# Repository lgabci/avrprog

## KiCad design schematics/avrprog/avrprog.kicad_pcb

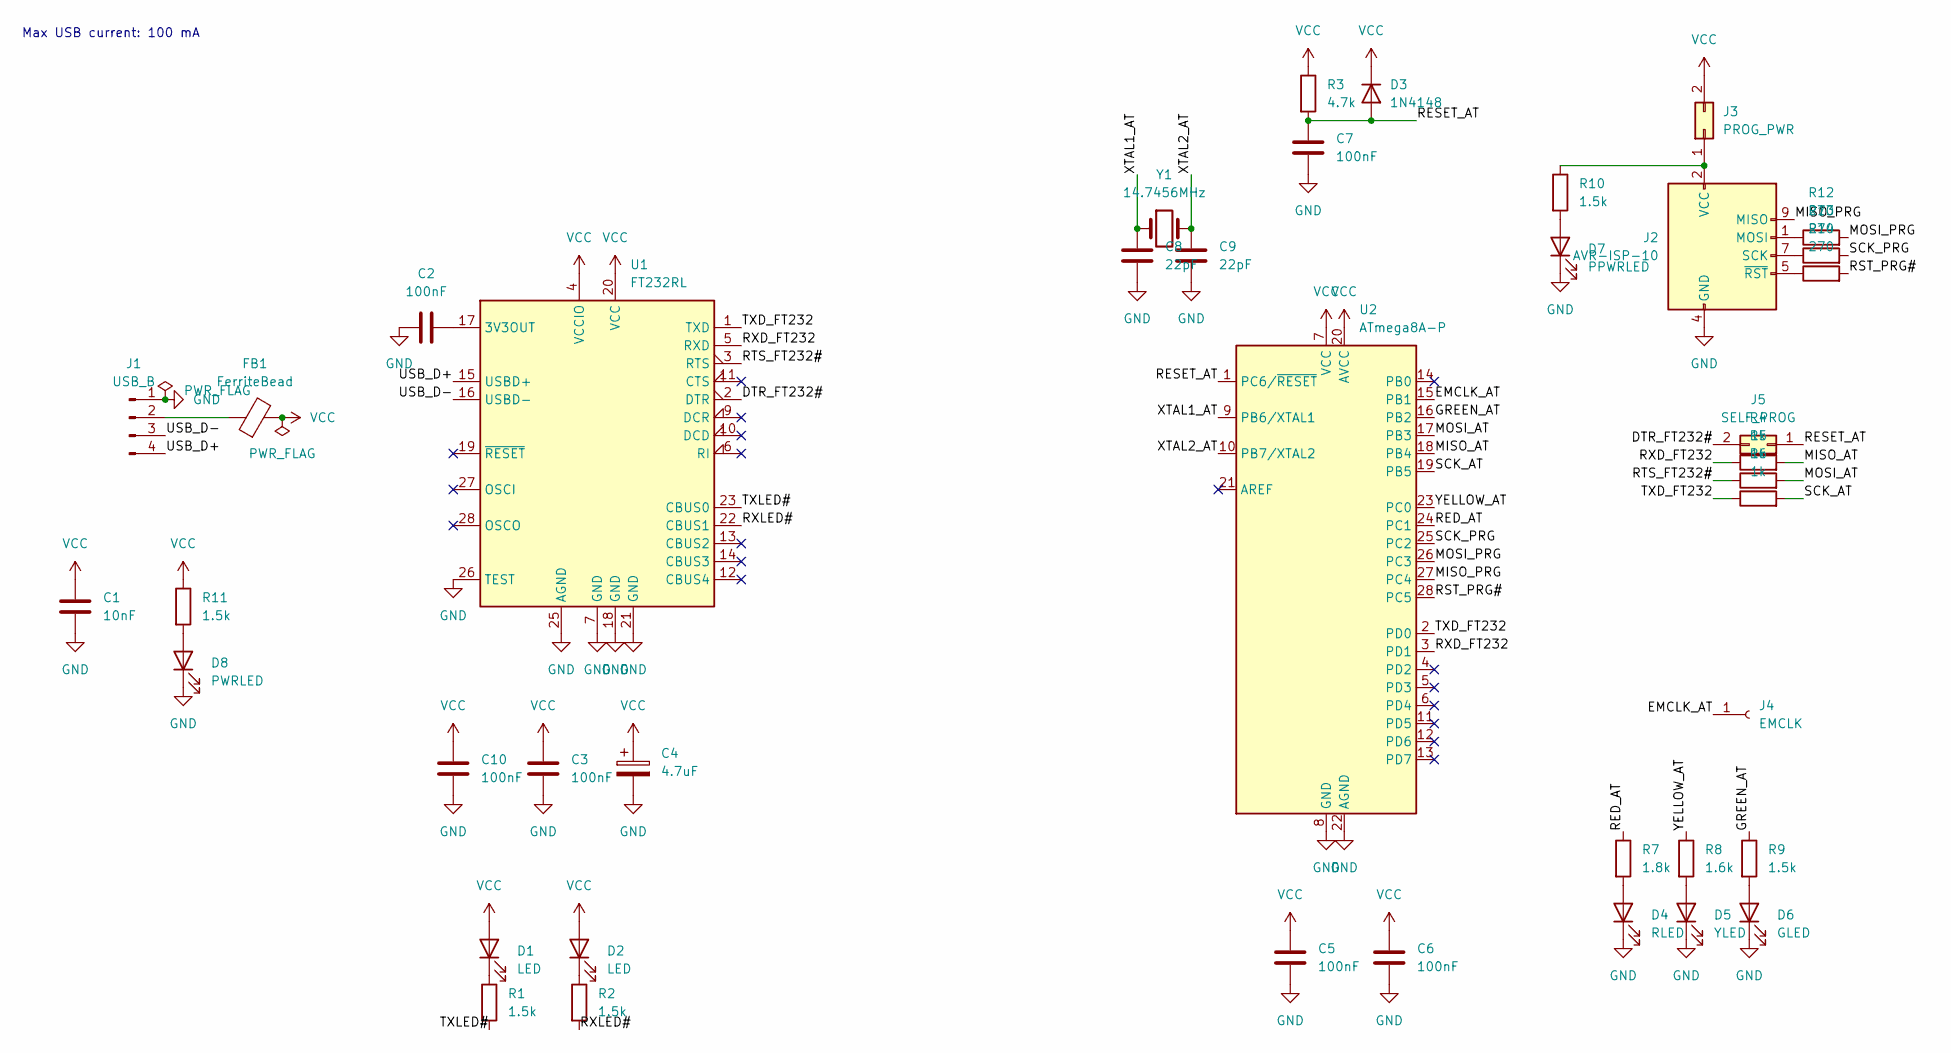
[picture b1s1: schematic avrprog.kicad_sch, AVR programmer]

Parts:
C1: 10nF; C_Disc_D3.8mm_W2.6mm_P2.50mm
C2, C3, C5, C6, C7, C10: 100nF; C_Disc_D3.8mm_W2.6mm_P2.50mm
C4: 4.7uF; CP_Radial_D5.0mm_P2.00mm
C8, C9: 22pF; C_Disc_D3.8mm_W2.6mm_P2.50mm
D1, D2: LED; LED_D3.0mm
D3: 1N4148; D_DO-35_SOD27_P7.62mm_Horizontal
D4: RLED; LED_D3.0mm
D5: YLED; LED_D3.0mm
D6: GLED; LED_D3.0mm
D7: PPWRLED; LED_D3.0mm
D8: PWRLED; LED_D3.0mm
FB1: FerriteBead; R_0805_2012Metric_Pad1.20x1.40mm_HandSolder
J1: USB_B; PinHeader_1x04_P2.54mm_Vertical
J2: AVR-ISP-10; PinSocket_2x05_P2.54mm_Vertical
J3: PROG_PWR; PinHeader_1x02_P2.54mm_Vertical
J4: EMCLK; PinSocket_1x01_P2.54mm_Vertical
J5: SELF_PROG; PinHeader_1x02_P2.54mm_Vertical
R1, R2, R9, R10, R11: 1.5k; R_Axial_DIN0207_L6.3mm_D2.5mm_P10.16mm_Horizontal
R3: 4.7k; R_Axial_DIN0207_L6.3mm_D2.5mm_P10.16mm_Horizontal
R4, R5, R6: 1k; R_Axial_DIN0207_L6.3mm_D2.5mm_P10.16mm_Horizontal
R7: 1.8k; R_Axial_DIN0207_L6.3mm_D2.5mm_P10.16mm_Horizontal
R8: 1.6k; R_Axial_DIN0207_L6.3mm_D2.5mm_P10.16mm_Horizontal
R12, R13, R14: 270; R_Axial_DIN0207_L6.3mm_D2.5mm_P10.16mm_Horizontal
U1: FT232RL; DIP-28_W15.24mm_Socket_LongPads
U2: ATmega8A-P; DIP-28_W7.62mm_Socket_LongPads
Y1: 14.7456MHz; Crystal_HC49-U_Vertical

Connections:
/DTR_FT232#: J5.2, U1.2 (DTR)
/EMCLK_AT: J4.1, U2.15 (PB1)
/GREEN_AT: R9.1, U2.16 (PB2)
/MISO_AT: R4.2, U2.18 (PB4)
/MISO_PRG: J2.9 (MISO), U2.27 (PC4)
/MOSI_AT: R5.2, U2.17 (PB3)
/MOSI_PRG: R12.2, U2.26 (PC3)
/RED_AT: R7.1, U2.24 (PC1)
/RESET_AT: C7.2, D3.2 (A), J5.1, R3.2, U2.1 (PC6/~RESET)
/RST_PRG#: R14.2, U2.28 (PC5)
/RTS_FT232#: R5.1, U1.3 (RTS)
/RXD_FT232: R4.1, U1.5 (RXD), U2.3 (PD1)
/RXLED#: R2.2, U1.22 (CBUS1)
/SCK_AT: R6.2, U2.19 (PB5)
/SCK_PRG: R13.2, U2.25 (PC2)
/TXD_FT232: R6.1, U1.1 (TXD), U2.2 (PD0)
/TXLED#: R1.2, U1.23 (CBUS0)
/USB_D+: J1.4, U1.15 (USBD+)
/USB_D-: J1.3, U1.16 (USBD-)
/XTAL1_AT: C8.2, U2.9 (PB6/XTAL1), Y1.1
/XTAL2_AT: C9.2, U2.10 (PB7/XTAL2), Y1.2
/YELLOW_AT: R8.1, U2.23 (PC0)
GND: C1.2, C2.1, C3.1, C4.2, C5.1, C6.1, C7.1, C8.1, C9.1, C10.1, D4.1 (K), D5.1 (K), D6.1 (K), D7.1 (K), D8.1 (K), J1.1, J2.4 (GND), J2.6 (GND), J2.8 (GND), J2.10 (GND), U1.7 (GND), U1.18 (GND), U1.21 (GND), U1.25 (AGND), U1.26 (TEST), U2.8 (GND), U2.22 (AGND)
unnamed: C2.2, U1.17 (3V3OUT)
unnamed: D1.1 (K), R1.1
unnamed: D2.1 (K), R2.1
unnamed: D4.2 (A), R7.2
unnamed: D5.2 (A), R8.2
unnamed: D6.2 (A), R9.2
unnamed: D7.2 (A), R10.2
unnamed: D8.2 (A), R11.2
unnamed: FB1.1, J1.2
unnamed: J2.1 (MOSI), R12.1
unnamed: J2.2 (VCC), J3.1, R10.1
unnamed: J2.5 (~RST), R14.1
unnamed: J2.7 (SCK), R13.1
VCC: C1.1, C3.2, C4.1, C5.2, C6.2, C10.2, D1.2 (A), D2.2 (A), D3.1 (K), FB1.2, J3.2, R3.1, R11.1, U1.4 (VCCIO), U1.20 (VCC), U2.7 (VCC), U2.20 (AVCC)

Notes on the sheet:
Max USB current: 100 mA

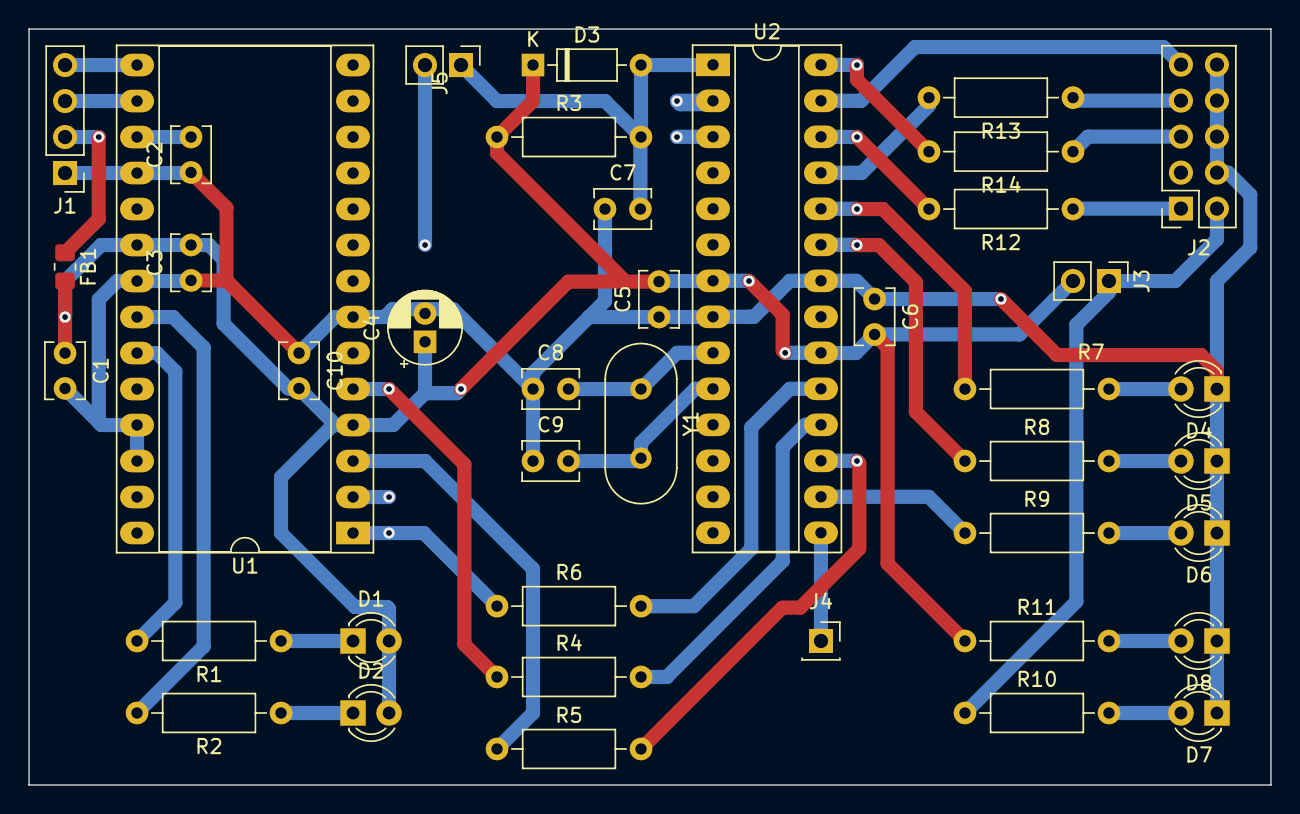
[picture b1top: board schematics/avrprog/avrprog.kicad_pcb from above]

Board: 2 copper layers, 87.6 x 53.3 mm, 41 parts (0 on the bottom side), 37 nets.

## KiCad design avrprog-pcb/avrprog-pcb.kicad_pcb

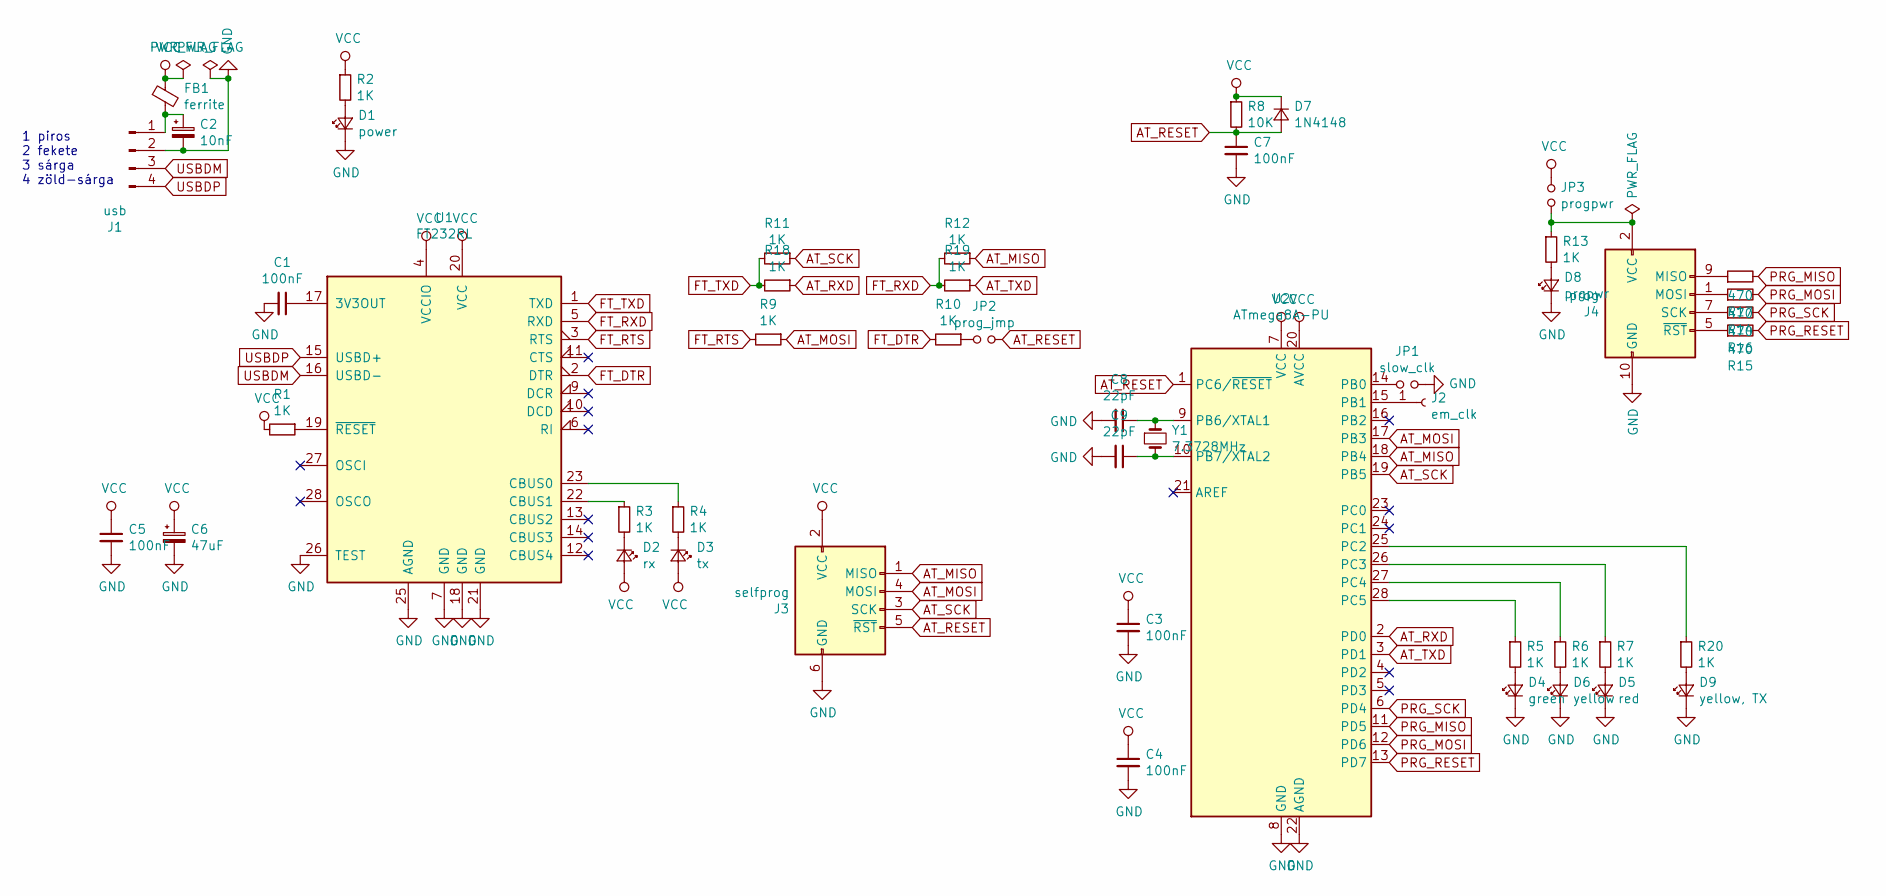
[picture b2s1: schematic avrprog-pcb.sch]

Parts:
C1, C3, C4, C5, C7: 100nF; C_Rect_L7.2mm_W2.5mm_P5.00mm_FKS2_FKP2_MKS2_MKP2
C2: 10nF; C_Disc_D5.0mm_W2.5mm_P2.50mm
C6: 47uF; CP_Radial_D6.3mm_P2.50mm
C8, C9: 22pF; C_Disc_D5.0mm_W2.5mm_P2.50mm
D1: power; LED_D3.0mm
D2: rx; LED_D3.0mm
D3: tx; LED_D3.0mm
D4: green; LED_D3.0mm
D5: red; LED_D3.0mm
D6: yellow; LED_D3.0mm
D7: 1N4148; D_DO-35_SOD27_P7.62mm_Horizontal
D8: prgpwr; LED_D3.0mm
D9: yellow, TX; LED_D3.0mm
FB1: ferrite; L_0805_2012Metric_Pad1.15x1.40mm_HandSolder
J1: usb; PinHeader_1x04_P2.54mm_Horizontal
J2: em_clk; PinSocket_1x01_P2.54mm_Vertical
J3: selfprog; PinHeader_2x03_P2.54mm_Vertical
J4: prog; PinHeader_2x05_P2.54mm_Vertical
JP1: slow_clk; PinHeader_1x02_P2.54mm_Vertical
JP2: prog_jmp; PinHeader_1x02_P2.54mm_Vertical
JP3: progpwr; PinHeader_1x02_P2.54mm_Vertical
R1, R2, R3, R4, R5, R6, R7, R9, R10, R11, R12, R13, R18, R19, R20: 1K; R_Axial_DIN0207_L6.3mm_D2.5mm_P7.62mm_Horizontal
R8: 10K; R_Axial_DIN0207_L6.3mm_D2.5mm_P7.62mm_Horizontal
R14, R15, R16, R17: 470; R_Axial_DIN0207_L6.3mm_D2.5mm_P7.62mm_Horizontal
U1: FT232RL; DIP-28_W15.24mm
U2: ATmega8A-PU; DIP-28_W7.62mm
Y1: 7.3728MHz; Crystal_HC49-U_Vertical

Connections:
AT_MISO: J3.1 (MISO), R12.1, U2.18 (PB4)
AT_MOSI: J3.4 (MOSI), R9.1, U2.17 (PB3)
AT_RESET: C7.1, D7.2 (A), J3.5 (~RST), JP2.2, R8.2, U2.1 (PC6/~RESET)
AT_RXD: R18.1, U2.2 (PD0)
AT_SCK: J3.3 (SCK), R11.1, U2.19 (PB5)
AT_TXD: R19.1, U2.3 (PD1)
FT_DTR: R10.2, U1.2 (DTR)
FT_RTS: R9.2, U1.3 (RTS)
FT_RXD: R12.2, R19.2, U1.5 (RXD)
FT_TXD: R11.2, R18.2, U1.1 (TXD)
GND: C1.2, C2.2, C3.2, C4.2, C5.2, C6.2, C7.2, C8.2, C9.2, D1.1 (K), D4.1 (K), D5.1 (K), D6.1 (K), D8.1 (K), D9.1 (K), J1.2, J3.6 (GND), J4.4 (GND), J4.6 (GND), J4.8 (GND), J4.10 (GND), JP1.2, U1.7 (GND), U1.18 (GND), U1.21 (GND), U1.25 (AGND), U1.26 (TEST), U2.8 (GND), U2.22 (AGND)
unnamed: C1.1, U1.17 (3V3OUT)
unnamed: C2.1, FB1.2, J1.1
unnamed: C8.1, U2.9 (PB6/XTAL1), Y1.1
unnamed: C9.1, U2.10 (PB7/XTAL2), Y1.2
unnamed: D1.2 (A), R2.2
unnamed: D2.1 (K), R3.2
unnamed: D3.1 (K), R4.2
unnamed: D4.2 (A), R5.2
unnamed: D5.2 (A), R7.2
unnamed: D6.2 (A), R6.2
unnamed: D8.2 (A), R13.2
unnamed: D9.2 (A), R20.2
unnamed: J2.1, U2.15 (PB1)
unnamed: J4.1 (MOSI), R14.1
unnamed: J4.2 (VCC), JP3.2, R13.1
unnamed: J4.5 (~RST), R15.1
unnamed: J4.7 (SCK), R16.1
unnamed: J4.9 (MISO), R17.1
unnamed: JP1.1, U2.14 (PB0)
unnamed: JP2.1, R10.1
unnamed: R1.1, U1.19 (~RESET~)
unnamed: R3.1, U1.22 (CBUS1)
unnamed: R4.1, U1.23 (CBUS0)
unnamed: R5.1, U2.28 (PC5)
unnamed: R6.1, U2.27 (PC4)
unnamed: R7.1, U2.26 (PC3)
unnamed: R20.1, U2.25 (PC2)
PRG_MISO: R17.2, U2.11 (PD5)
PRG_MOSI: R14.2, U2.12 (PD6)
PRG_RESET: R15.2, U2.13 (PD7)
PRG_SCK: R16.2, U2.6 (PD4)
USBDM: J1.3, U1.16 (USBD-)
USBDP: J1.4, U1.15 (USBD+)
VCC: C3.1, C4.1, C5.1, C6.1, D2.2 (A), D3.2 (A), D7.1 (K), FB1.1, J3.2 (VCC), JP3.1, R1.2, R2.1, R8.1, U1.4 (VCCIO), U1.20 (VCC), U2.7 (VCC), U2.20 (AVCC)

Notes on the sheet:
1 piros 2 fekete 3 sárga 4 zöld-sárga

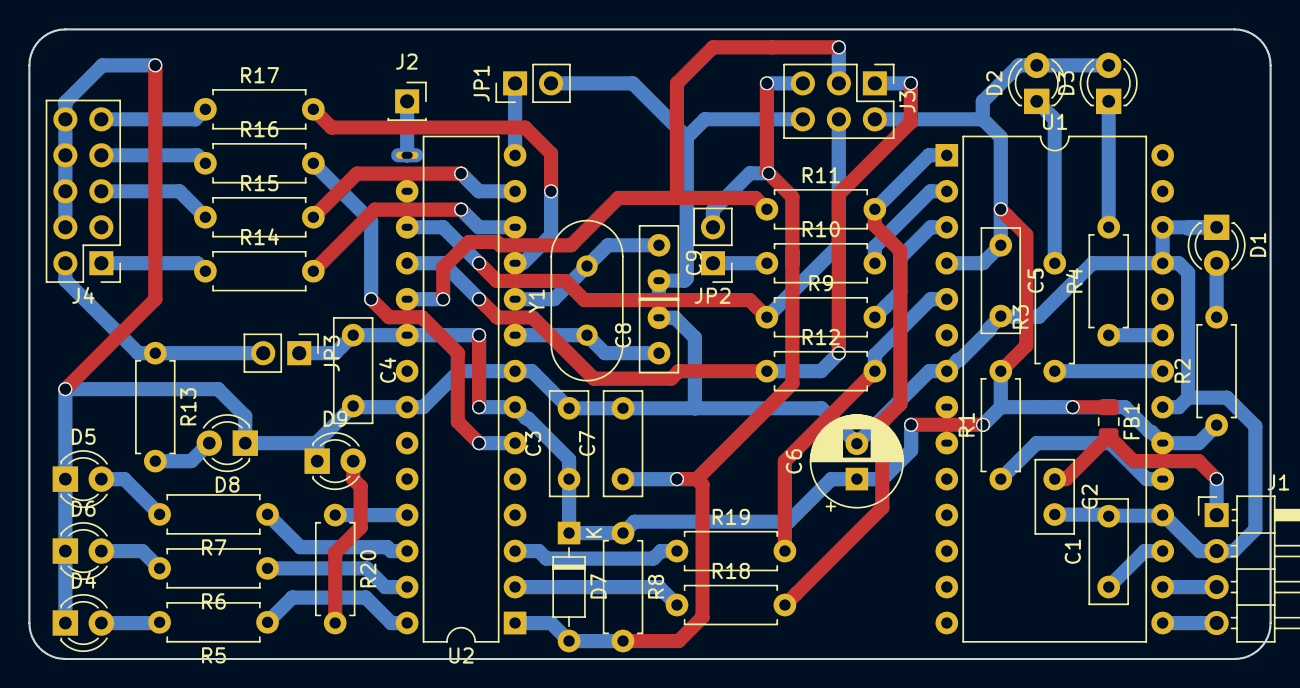
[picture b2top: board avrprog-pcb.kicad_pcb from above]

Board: 2 copper layers, 87.6 x 44.5 mm, 49 parts (0 on the bottom side), 45 nets.

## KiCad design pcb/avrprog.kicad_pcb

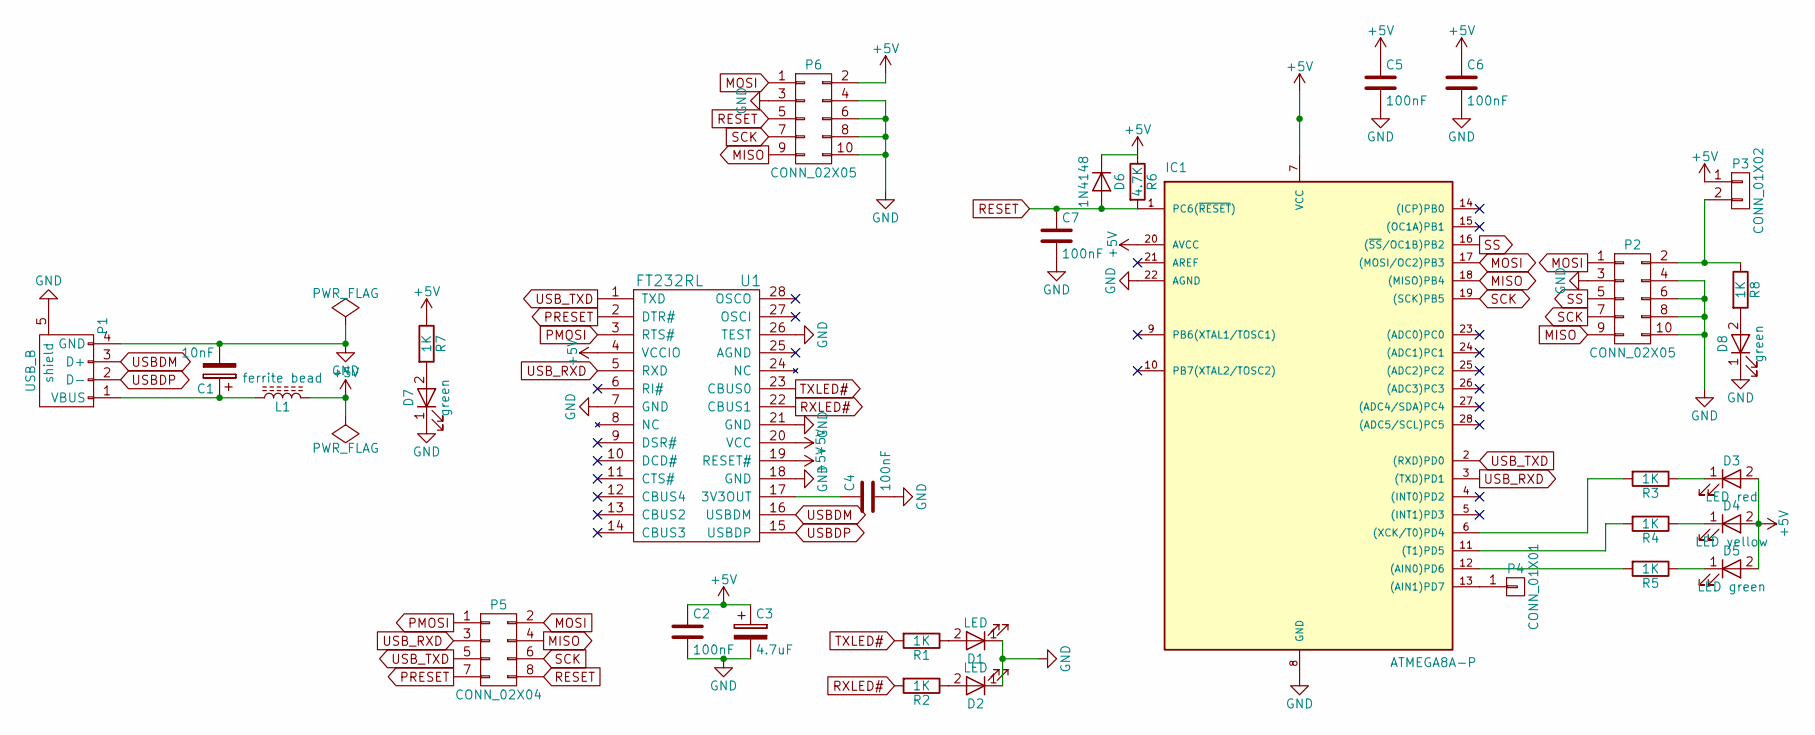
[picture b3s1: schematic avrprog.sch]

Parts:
C1: 10nF; C_Radial_D5_L11_P2.5
C2, C4, C5, C6, C7: 100nF; C_Rect_L7_W2_P5
C3: 4.7uF; C_Radial_D5_L11_P2.5
D1, D2: LED; LED-3MM
D3: LED red; LED-3MM
D4: LED yellow; LED-3MM
D5: LED green; LED-3MM
D6: 1N4148; Diode_DO-35_SOD27_Horizontal_RM10
D7, D8: green; LED-3MM
IC1: ATMEGA8A-P; DIP-28_W7.62mm
L1: ferrite bead; Choke_Horizontal_RM10mm
P1: USB_B
P2, P6: CONN_02X05; Pin_Header_Straight_2x05
P3: CONN_01X02; Pin_Header_Straight_1x02
P4: CONN_01X01; Pin_Header_Straight_1x01
P5: CONN_02X04; Pin_Header_Straight_2x04
R1, R2, R3, R4, R5, R7, R8: 1K; Resistor_Horizontal_RM10mm
R6: 4.7K; Resistor_Horizontal_RM10mm
U1: FT232RL; SSOP-28_5.3x10.2mm_Pitch0.65mm

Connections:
+5V: C2.1, C3.1, C5.1, C6.1, D3.2 (A), D4.2 (A), D5.2 (A), D6.1 (K), IC1.7 (VCC), IC1.20 (AVCC), L1.2, P3.1, P6.2, R6.1, R7.1, U1.4 (VCCIO), U1.19 (RESET#), U1.20 (VCC)
GND: C1.2, C2.2, C3.2, C4.2, C5.2, C6.2, C7.2, D1.1 (K), D2.1 (K), D7.1 (K), D8.1 (K), IC1.8 (GND), IC1.22 (AGND), P1.4 (GND), P1.5 (shield), P2.3, P2.4, P2.6, P2.8, P2.10, P6.3, P6.4, P6.6, P6.8, P6.10, U1.7 (GND), U1.18 (GND), U1.21 (GND), U1.26 (TEST)
MISO: IC1.18 ((MISO)PB4), P2.9, P5.4, P6.9
MOSI: IC1.17 ((MOSI/OC2)PB3), P2.1, P5.2, P6.1
unnamed: C1.1, L1.1, P1.1 (VBUS)
unnamed: C4.1, U1.17 (3V3OUT)
unnamed: D1.2 (A), R1.1
unnamed: D2.2 (A), R2.1
unnamed: D3.1 (K), R3.1
unnamed: D4.1 (K), R4.1
unnamed: D5.1 (K), R5.1
unnamed: D7.2 (A), R7.2
unnamed: D8.2 (A), R8.2
unnamed: IC1.6 ((XCK/T0)PD4), R3.2
unnamed: IC1.11 ((T1)PD5), R4.2
unnamed: IC1.12 ((AIN0)PD6), R5.2
unnamed: IC1.13 ((AIN1)PD7), P4.1
unnamed: P2.2, P3.2, R8.1
PMOSI: P5.1, U1.3 (RTS#)
PRESET: P5.7, U1.2 (DTR#)
RESET: C7.1, D6.2 (A), IC1.1 (PC6(~RESET~)), P5.8, P6.5, R6.2
RXLED#: R2.2, U1.22 (CBUS1)
SCK: IC1.19 ((SCK)PB5), P2.7, P5.6, P6.7
SS: IC1.16 ((~SS~/OC1B)PB2), P2.5
TXLED#: R1.2, U1.23 (CBUS0)
USBDM: P1.3 (D+), U1.16 (USBDM)
USBDP: P1.2 (D-), U1.15 (USBDP)
USB_RXD: IC1.3 ((TXD)PD1), P5.3, U1.5 (RXD)
USB_TXD: IC1.2 ((RXD)PD0), P5.5, U1.1 (TXD)

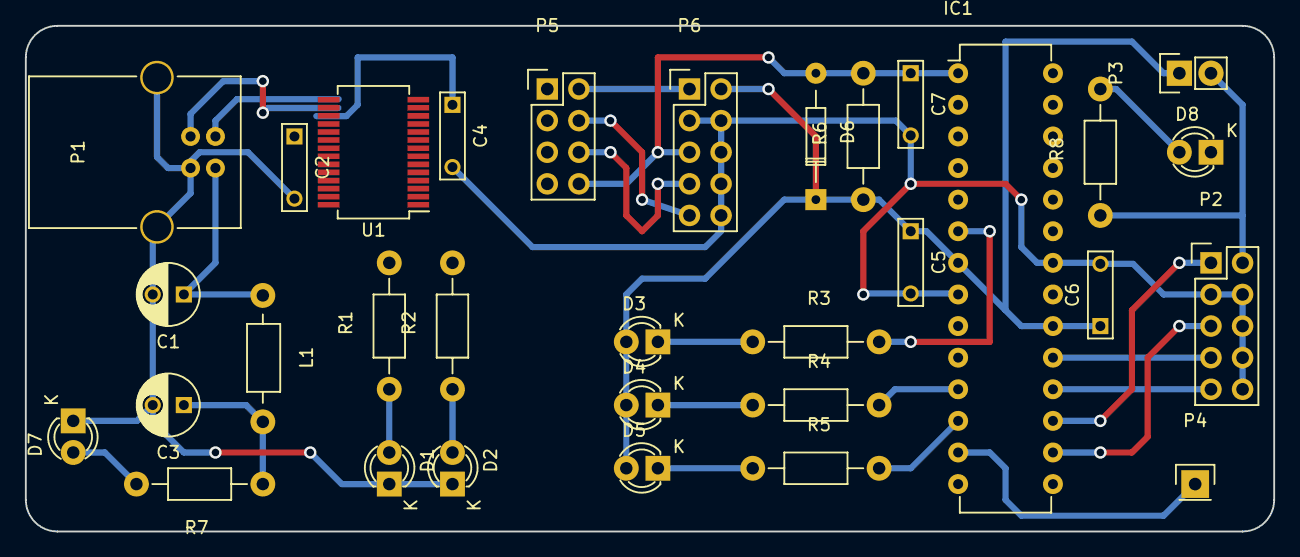
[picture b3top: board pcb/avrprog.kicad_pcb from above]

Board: 2 copper layers, 100.3 x 40.6 mm, 32 parts (0 on the bottom side), 29 nets.

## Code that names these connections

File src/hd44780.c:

/* AVR programmer HD44780 */

#include "common.h"

#include <avr/io.h>
#include <util/delay.h>

#include "hd44780.h"

/* used port */
#define PORTLCD PORTC

#define B0 PC0
#define B1 PC1
#define B2 PC2
#define B3 PC3
#define RS PC4
#define EN PC5

/* commands */
#define CMDCLS     0x01  /* clear display           */
#define CMDHOME    0x02  /* return home             */
#define CMDEMODE   0x04  /* entry mode set          */
#define CMDDONOFF  0x08  /* display on/off control  */
#define CMDSHIFT   0x10  /* cursor or display shift */
#define CMDFNCSET  0x20  /* function set            */
#define CMDSETCADD 0x40  /* set CGRAM address       */
#define CMDSETDADD 0x80  /* set DDRAM address       */

/* waiting for commands to complete */
#define DELAYCLS     _delay_ms(10)
#define DELAYHOME    _delay_ms(1.52)
#define DELAYEMODE   _delay_us(37)
#define DELAYDONOFF  _delay_us(37)
#define DELAYSHIFT   _delay_us(37)
#define DELAYFNCSET  _delay_us(37)
#define DELAYSETCADD _delay_us(37)
#define DELAYSETDADD _delay_us(37)

#define DELAYWRTDATA _delay_us(37 + 4)

/* bit positions for commands */
#define BITS  0 /* 0 = don't shift, 1 = shift */
#define BITID 1 /* 0 = dec, 1 = inc */
#define BITB  0 /* screen 0 = off, 1 = on */
#define BITC  1 /* cursor 0 = off, 1 = on */
#define BITD  2 /* blink  0 = off, 1 = on */
#define BITRL 2 /* 0 = left, 1 = right */
#define BITSC 3 /* 0 = cursor move, 1 = display shift */
#define BITF  2 /* font: 0 = 5x8 dot, 1 = 5x10 dots */
#define BITN  3 /* 0 = 1 line, 1 = 2 lines */
#define BITDL 4 /* 0 = 4 bits, 1 = 8 bits */

/* timing values in microseconds */
#define tcycE 0.500
#define PWEH  0.230
#define tAS   0.40
#define tAH   0.10
#define tDSW  0.80
#define tH    0.10

void sendNibble(const unsigned char rs, const  unsigned char n);
void sendByte(const unsigned char rs, const unsigned char n);

void initLcd(void) {
  DDRC = 0x3f;					/* PC0-PC5 output */

  _delay_ms(15);
  sendNibble(0, (CMDFNCSET | _BV(BITDL)) >> 4); /* function set */
  _delay_ms(5);
  sendNibble(0, (CMDFNCSET | _BV(BITDL)) >> 4); /* function set */
  _delay_us(200);
  sendNibble(0, (CMDFNCSET | _BV(BITDL)) >> 4); /* function set */
  DELAYFNCSET;
  sendNibble(0, (CMDFNCSET) >> 4); /* function set: 4 bit interface */
  DELAYFNCSET;
  sendByte(0, CMDFNCSET | _BV(BITN) ); /* f. set: 4 bit, 2 lines, 5x8 dot */
  DELAYFNCSET;
  sendByte(0, CMDDONOFF);                        /* display off */
  DELAYDONOFF;
  sendByte(0, CMDCLS);                          /* clear screen */
  DELAYCLS;
  sendByte(0, CMDEMODE | _BV(BITID));    /* entry mode set, don't shift */
  DELAYEMODE;

  sendByte(0, CMDDONOFF | _BV(BITD) | _BV(BITC) | _BV(BITB)); /* display on */
  DELAYDONOFF;
}

void writeChr(const char c) {
  sendByte(1, c);
  DELAYWRTDATA;
}

void writeStr(const char *c) {
  while (*c) {
    writeChr(*c);
    c ++;
  }
}

void setPos(const unsigned char col, const unsigned char row) {
  sendByte(0, CMDSETDADD | (((row << 6) + col) & (CMDSETDADD - 1)));
  DELAYSETDADD;
}

void sendNibble(const unsigned char rs, const unsigned char n) {
/* timing

   Item                                 Symbol     Min     Typ     Max     Unit
   ------------------------------------ ---------- ------- ------- ------- -------
   Enable cycle time                    tcycE      500     -       -       ns
   Enable pulse width (high level)      PWEH       230     -       -
   Enable rise/fall time                tEr, tEf   -       -       20
   Address set-up time (RS, R/W to E)   tAS        40      -       -
   Address hold time                    tAH        10      -       -
   Data set-up time                     tDSW       80      -       -
   Data hold time                       tH         10      -       -
     _
   R/W is always on GND, we don't set it.

             ____ ____________________________________ ___________
          RS ____X____________________________________X___________
                 :                                    :
                 <-- tAS -->                <-- tAH -->
           _ ____:         :                :         :___________
         R/W ____\____________________________________/___________
                 :         :                :
                           <----- PWEH ----->
                           :________________:                 ____
          E  ______________/                \________________/   
                        -->:<-- tEr      -->:<-- tEf         :
                           :     <-- tDSW --x-- tH --->      :
             ____________________:____________________:___________
   DB0 - DB7 ____________________X____________________X___________
                           :                                 :
                           <------------- tcycE ------------->
 */
  PORTLCD = (n & (_BV(B0) | _BV(B1) | _BV(B2) | _BV(B3))) | (rs ? _BV(RS) : 0);
  _delay_us(tAS);
  PORTLCD |= _BV(EN);
  _delay_us(PWEH);
  PORTLCD &= ~_BV(EN);
  _delay_us(tcycE - PWEH - tAS);
}

void sendByte(const unsigned char rs, const unsigned char n) {
  sendNibble(rs, n >> 4);
  sendNibble(rs, n);
}

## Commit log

2019-02-13 hardware test: 1 sec LED blinker
2019-04-19 schematic (not finished yet)
2019-04-20 schematic (not finished)
2019-04-22 pcb creation with kicad (not finished)
2019-04-28 pcb (not finished)
2019-05-02 pcb (gEDA schematic added)
2019-05-04 - in schematic turn to geda - program odified to use 7.3728 MHz crystal instead of 8MHz internal osc
2019-05-04 stk500 communication, send and receive messages, some stk500 commands tested
2019-05-05 PCB footprints added
2019-05-06 1MHz clock output conencted to PB1(OC1A)
2019-05-07 PWM on PB1
2019-05-08 emergency clock signal: 921600 Hz 50% PWM on PB1, finished
2019-05-11 set PARAM_RESET_POLARITY; test output
2019-05-12 SPI testing
2019-05-15 software SPI, not finished
2019-05-20 decompose avrprog.c into multiple .c files by content
2019-05-23 headers added to C source makefile modified for multiple source files
2019-06-04 PCB: using software SPI (PC2-PC5) insteod of hardware SPI
2019-06-08 component and wires rearrangement
2019-06-09 PCB designing
2019-06-09 PCB finished
2019-11-26 HD44780 char LCD support added for debug purposes
2019-11-26 Introduction of Autotools
2019-12-01 types changed (int -> int16_t, char -> int8_t, unsigned char ->uint8_t) added: CMD_LOAD_ADDRESS, CMD READ_FLASH
2019-12-07 message and prog modified
2019-12-12 using meson + ninja instead of autotools
2019-12-17 back to Makefile
2019-12-19 timing: spiClockDelay
2019-12-21 prog.c: reordered, EEPROM handling, spi.c: nowait transmission
2019-12-22 new funcs in prog.c: sign on, firmware upgrade, read and write lock bits
2019-12-25 spi.c: fix some bugs in transmission; prog.c: readOsccal, spiMulti
2019-12-28 LCD display removed, 4 LEDs added
2020-05-05 schematics redesigned
2020-05-06 resistor value changed to 1K between FT232RL and ATmega reset pin some small visual modifications
2020-05-06 transitioning to KiCad
2020-05-07 creating PCB
2020-05-08 designing PCB
2020-05-15 PCB redesigned for smaller size transition from make to meson + ninja
2020-05-16 some fixes for flashing
2021-03-07 minor schematics fixes
2021-04-06 schematics and PCB mod
2021-04-07 schematics and PCB mod connector ISP connector 10 to 6
2024-03-17 .gitinore added
2024-03-17 schematics/avrprog/.gitignore added
2024-03-17 schematic ...
2024-03-29 schematics completed
2024-03-30 crystal changed from 16MHz to 14.7456MHz due to USART communication
2024-09-29 PCB reorganized
2024-10-05 simple PCB correction
